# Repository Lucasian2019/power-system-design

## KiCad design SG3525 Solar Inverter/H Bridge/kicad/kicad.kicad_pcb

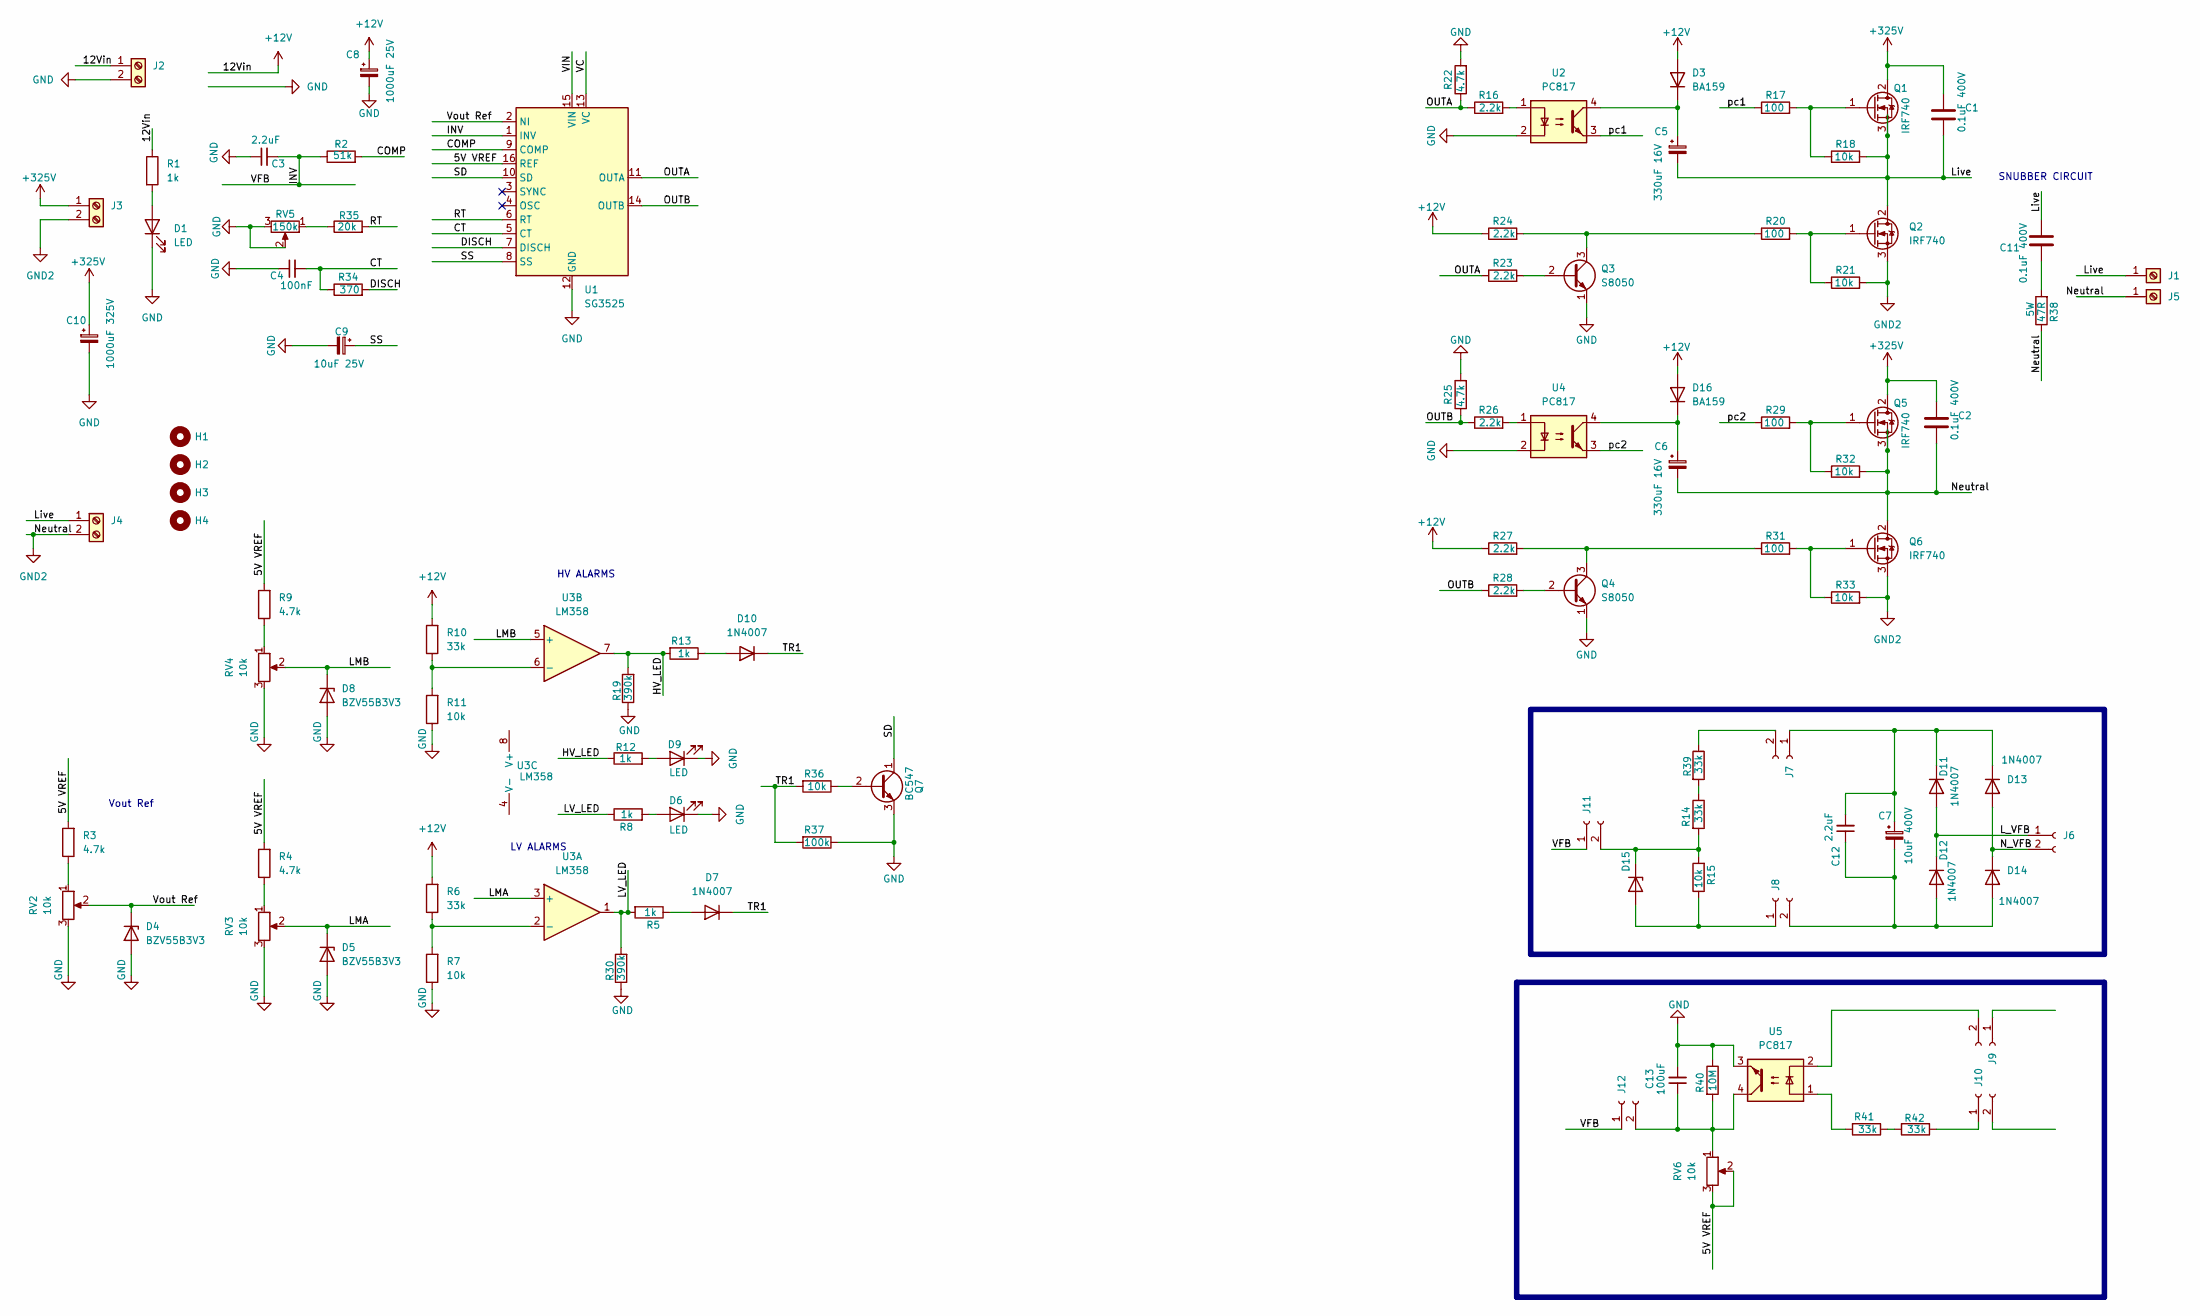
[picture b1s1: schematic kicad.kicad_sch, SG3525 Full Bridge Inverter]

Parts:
C1, C2, C11: 0.1uF 400V; C_Rect_L13.5mm_W5.0mm_P10.00mm_FKS3_FKP3_MKS4
C3, C12: 2.2uF; C_Disc_D7.0mm_W2.5mm_P5.00mm
C4: 100nF; C_Disc_D7.0mm_W2.5mm_P5.00mm
C5, C6: 330uF 16V; C_Radial_D5.0mm_H11.0mm_P2.00mm
C7: 10uF 400V; C_Radial_D5.0mm_H11.0mm_P2.00mm
C8: 1000uF 25V; C_Radial_D10.0mm_H12.5mm_P5.00mm
C9: 10uF 25V; C_Radial_D5.0mm_H11.0mm_P2.00mm
C10: 1000uF 325V; C_Radial_D10.0mm_H12.5mm_P5.00mm
C13: 100uF; C_Disc_D7.0mm_W2.5mm_P5.00mm
D1, D6, D9: LED; LED_D5.0mm
D3, D16: BA159; D_DO-41_SOD81_P10.16mm_Horizontal
D4, D5, D8, D15: BZV55B3V3; D_DO-35_SOD27_P7.62mm_Horizontal
D7, D10, D11, D12, D13, D14: 1N4007; D_DO-41_SOD81_P10.16mm_Horizontal
H1, H2, H3, H4: MountingHole; MountingHole_3.2mm_M3_Pad_Via
J1, J5: Screw_Terminal_01x01; SolderWire-0.127sqmm_1x01_D0.48mm_OD1mm
J2, J3, J4: Screw_Terminal_01x02; TerminalBlock_Phoenix_PT-1,5-2-5.0-H_1x02_P5.00mm_Horizontal
J6, J7, J8, J9, J10, J11, J12: Conn_01x02_Socket; PinHeader_1x02_P2.54mm_Vertical
Q1, Q2, Q5, Q6: IRF740; TO-220-3_Vertical
Q3, Q4: S8050; TO-92_Inline
Q7: BC547; TO-92_Inline
R1, R5, R8, R12, R13: 1k; R_Axial_DIN0207_L6.3mm_D2.5mm_P7.62mm_Horizontal
R2: 51k; R_Axial_DIN0207_L6.3mm_D2.5mm_P7.62mm_Horizontal
R3, R4, R9, R22, R25: 4.7k; R_Axial_DIN0207_L6.3mm_D2.5mm_P7.62mm_Horizontal
R6, R10, R14, R39, R41, R42: 33k; R_Axial_DIN0207_L6.3mm_D2.5mm_P7.62mm_Horizontal
R7, R11, R15, R18, R21, R32, R33, R36: 10k; R_Axial_DIN0207_L6.3mm_D2.5mm_P7.62mm_Horizontal
R16, R23, R24, R26, R27, R28: 2.2k; R_Axial_DIN0207_L6.3mm_D2.5mm_P7.62mm_Horizontal
R17, R20, R29, R31: 100; R_Axial_DIN0207_L6.3mm_D2.5mm_P7.62mm_Horizontal
R19, R30: 390k; R_Axial_DIN0207_L6.3mm_D2.5mm_P7.62mm_Horizontal
R34: 370; R_Axial_DIN0207_L6.3mm_D2.5mm_P7.62mm_Horizontal
R35: 20k; R_Axial_DIN0207_L6.3mm_D2.5mm_P7.62mm_Horizontal
R37: 100k; R_Axial_DIN0207_L6.3mm_D2.5mm_P7.62mm_Horizontal
R38: 47R; R_Axial_Power_L25.0mm_W6.4mm_P30.48mm
R40: 10M; R_Axial_DIN0207_L6.3mm_D2.5mm_P7.62mm_Horizontal
RV2, RV3, RV4, RV6: 10k; Potentiometer_Bourns_3296W_Vertical
RV5: 150k; Potentiometer_Bourns_3296W_Vertical
U1: SG3525; DIP-16_W7.62mm
U2, U4, U5: PC817; DIP-4_W7.62mm
U3: LM358; DIP-8_W7.62mm

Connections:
+12V: C8.1, D3.2 (A), D16.2 (A), J2.1, R1.1, R6.2, R10.2, R24.1, R27.1
+325V: C1.1, C2.1, C10.1, J3.1, Q1.2 (D), Q5.2 (D)
/5V VREF: R3.2, R4.2, R9.2, RV6.2, RV6.3, U1.16 (REF)
/COMP: R2.2, U1.9 (COMP)
/CT: C4.2, R34.1, U1.5 (CT)
/DISCH: R34.2, U1.7 (DISCH)
/HV_LED: R12.1, R13.2, R19.2, U3.7
/LMA: D5.1 (K), RV3.2, U3.3 (+)
/LMB: D8.1 (K), RV4.2, U3.5 (+)
/LV_LED: R5.2, R8.1, R30.2, U3.1
/L_VFB: D11.2 (A), D12.1 (K), J6.1
/Live: C1.2, C5.2, C11.2, J1.1 (Pin_1_1), J4.1, Q1.3 (S), Q2.2 (D), R18.2
/N_VFB: D13.2 (A), D14.1 (K), J6.2
/OUTA: R16.1, R22.1, R23.1, U1.11 (OUTA)
/OUTB: R25.1, R26.1, R28.1, U1.14 (OUTB)
/RT: R35.2, U1.6 (RT)
/SD: Q7.1 (C), U1.10 (SD)
/SS: C9.1, U1.8 (SS)
/TR1: D7.1 (K), D10.1 (K), R36.2, R37.2
/VC: U1.13 (VC)
/VIN: U1.15 (VIN)
/Vout Ref: D4.1 (K), RV2.2, U1.2 (NI)
/pc1: R17.1, U2.3
/pc2: R29.1, U4.3
GND: C3.1, C4.1, C8.2, C9.2, C10.2, C13.2, D1.1 (K), D4.2 (A), D5.2 (A), D6.1 (K), D8.2 (A), D9.1 (K), J2.2, Q3.1 (E), Q4.1 (E), Q7.3 (E), R7.1, R11.1, R19.1, R22.2, R25.2, R30.1, R37.1, R40.1, RV2.3, RV3.3, RV4.3, RV5.2, RV5.3, U1.12 (GND), U2.2, U4.2, U5.3
GND2: C2.2, C6.2, J3.2, J4.2, J5.1 (Pin_1_1), Q2.3 (S), Q5.3 (S), Q6.2 (D), Q6.3 (S), R21.2, R32.2, R33.2, R38.1
unnamed: C11.1, R38.2
unnamed: D1.2 (A), R1.2
unnamed: C5.1, D3.1 (K), U2.4
unnamed: D6.2 (A), R8.2
unnamed: D7.2 (A), R5.1
unnamed: D9.2 (A), R12.2
unnamed: D10.2 (A), R13.1
unnamed: C7.1, C12.2, D11.1 (K), D13.1 (K), J7.1
unnamed: C7.2, C12.1, D12.2 (A), D14.2 (A), J8.2
unnamed: D15.2 (A), J8.1, R15.1
unnamed: C6.1, D16.1 (K), U4.4
unnamed: J7.2, R39.1
unnamed: J9.2 (Pin_2_2), U5.2
unnamed: J10.1 (Pin_1_1), R42.1
unnamed: Q1.1 (G), R17.2, R18.1
unnamed: Q2.1 (G), R20.2, R21.1
unnamed: Q3.2 (B), R23.2
unnamed: Q3.3 (C), R20.1, R24.2
unnamed: Q4.2 (B), R28.2
unnamed: Q4.3 (C), R27.2, R31.1
unnamed: Q5.1 (G), R29.2, R32.1
unnamed: Q6.1 (G), R31.2, R33.1
unnamed: Q7.2 (B), R36.1
unnamed: R3.1, RV2.1
unnamed: R4.1, RV3.1
unnamed: R9.1, RV4.1
unnamed: R14.1, R39.2
unnamed: R16.2, U2.1
unnamed: R26.2, U4.1
unnamed: R35.1, RV5.1
unnamed: R41.1, R42.2
unnamed: R41.2, U5.1
unnamed: R6.1, R7.2, U3.2 (-)
unnamed: R10.1, R11.2, U3.6 (-)

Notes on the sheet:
HV ALARMS
LV ALARMS
Vout Ref
SNUBBER CIRCUIT

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
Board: 2 copper layers, 101 parts (0 on the bottom side), 59 nets, no tracks yet.
